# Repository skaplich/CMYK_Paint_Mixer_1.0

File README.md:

LOCKER : 91Y51          03-33-03

# CMYK_Paint_Mixer_1.0
ECE445 Project for FALL 2024

Color Sensor : https://www.adafruit.com/product/3779

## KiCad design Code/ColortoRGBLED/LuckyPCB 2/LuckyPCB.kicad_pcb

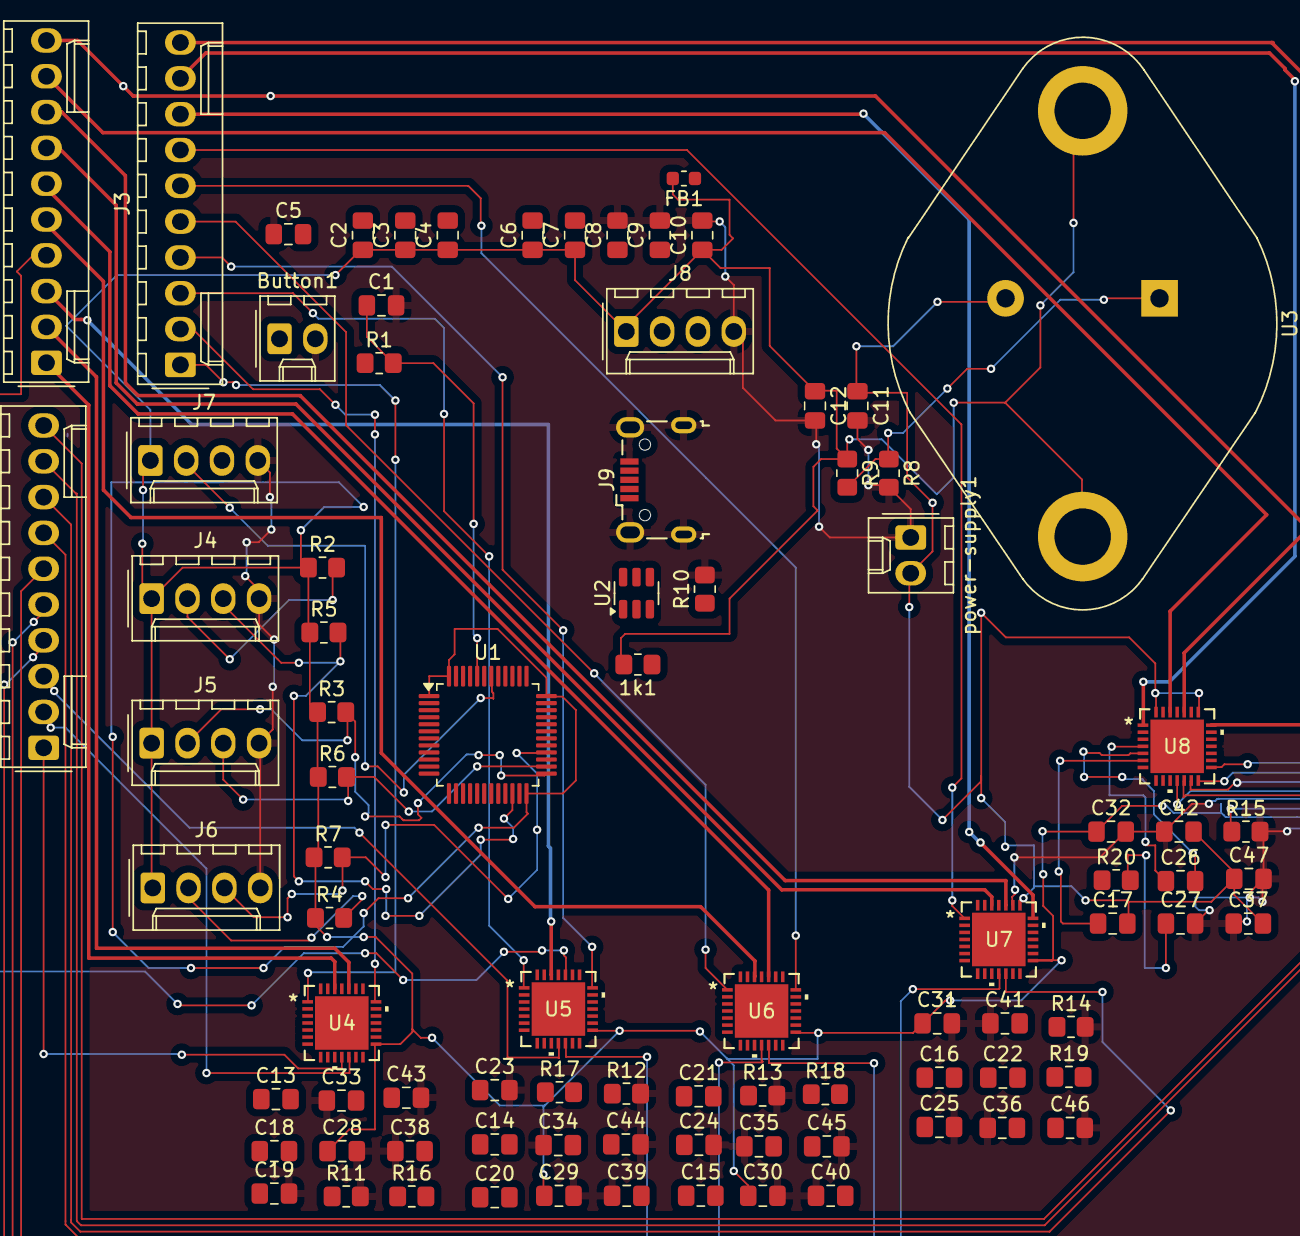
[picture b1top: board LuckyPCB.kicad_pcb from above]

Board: 2 copper layers, 88 parts (0 on the bottom side), 97 nets.

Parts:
1k1: R10; R_0805_2012Metric_Pad1.20x1.40mm_HandSolder
Button1: Conn_01x02; Molex_KK-254_AE-6410-02A_1x02_P2.54mm_Vertical
C1, C12: 1 uF; C_0805_2012Metric_Pad1.18x1.45mm_HandSolder
C2, C3, C4, C5, C6, C7, C33, C34, C35, C36, C37, C38, C39, C40, C41, C42: 100n; C_0805_2012Metric_Pad1.18x1.45mm_HandSolder
C8: 10n; C_0805_2012Metric_Pad1.18x1.45mm_HandSolder
C9, C10: 1u; C_0805_2012Metric_Pad1.18x1.45mm_HandSolder
C11: 0.1 uF; C_0805_2012Metric_Pad1.18x1.45mm_HandSolder
C13, C14, C15, C16, C17: 100 n/16v; C_0805_2012Metric_Pad1.18x1.45mm_HandSolder
C18, C20, C21, C22, C26: 22n/50v; C_0805_2012Metric_Pad1.18x1.45mm_HandSolder
C19, C23, C24, C25, C27: 2.2 uf; C_0805_2012Metric_Pad1.18x1.45mm_HandSolder
C28, C29, C30, C31, C32: 100n/50V; C_0805_2012Metric_Pad1.18x1.45mm_HandSolder
C43, C44, C45, C46, C47: 100 uF; C_0805_2012Metric_Pad1.18x1.45mm_HandSolder
FB1: FerriteBead; L_0603_1608Metric
J1, J2, J3: Conn_01x10_Pin; Molex_KK-254_AE-6410-10A_1x10_P2.54mm_Vertical
J4, J5, J6, J7, J8: Conn_01x04_Pin; Molex_KK-254_AE-6410-04A_1x04_P2.54mm_Vertical
J9: USB_B_Micro; USB_Micro-B_Wuerth_629105150521
R1: 10k; R_0805_2012Metric_Pad1.20x1.40mm_HandSolder
R2, R3, R4, R5, R6, R7: 1k5; R_0805_2012Metric_Pad1.20x1.40mm_HandSolder
R8: 390; R_0805_2012Metric_Pad1.20x1.40mm_HandSolder
R9: 240; R_0805_2012Metric_Pad1.20x1.40mm_HandSolder
R10: 100k; R_0805_2012Metric_Pad1.20x1.40mm_HandSolder
R11, R12, R13, R14, R15: 20k; R_0805_2012Metric_Pad1.20x1.40mm_HandSolder
R16, R17, R18, R19, R20: 18k; R_0805_2012Metric_Pad1.20x1.40mm_HandSolder
U1: STM32F103C8T6; LQFP-48_7x7mm_P0.5mm
U2: USBLC6-2SC6; SOT-23-6
U3: LM117_TO3; TO-3
U4, U5, U6, U7, U8: TMC2209-LA-T; QFN28_5X5_3X8_EPAD_TRI
power-supply1: Conn_01x02; Molex_KK-254_AE-6410-02A_1x02_P2.54mm_Vertical

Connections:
+3.3V: 1k1.2, C2.1, C3.1, C4.1, C6.1, C7.1, C10.1, C12.1, C28.1, C29.1, C30.1, C31.1, C32.1, FB1.2, J4.1, J5.1, J6.1, J7.1, J8.1, R2.1, R3.1, R4.1, R5.1, R6.1, R7.1, R9.1, U1.1 (VBAT), U1.24 (VDD), U1.36 (VDD), U1.48 (VDD), U3.3 (VO), U4.15 (VCC_IO), U5.15 (VCC_IO), U6.15 (VCC_IO), U7.15 (VCC_IO), U8.15 (VCC_IO)
+3.3VA: C8.1, C9.1, FB1.1, U1.9 (VDDA)
+24V: C11.1, C13.2, C14.2, C15.2, C16.2, C17.2, C33.2, C34.2, C35.2, C36.2, C37.2, C38.2, C39.2, C40.2, C41.2, C42.2, C43.1, C44.1, C45.1, C46.1, C47.1, U3.2 (VI), U4.22 (VS), U4.28 (VS), U5.22 (VS), U5.28 (VS), U6.22 (VS), U6.28 (VS), U7.22 (VS), U7.28 (VS), U8.22 (VS), U8.28 (VS), power-supply1.2
/I2C2_SCL: J4.2, R2.2, U1.21 (PB10)
/USART1_RX: J7.3, U1.43 (PB7)
DIAG-1: J2.1, U4.11 (DIAG)
DIAG-2: J2.3, U5.11 (DIAG)
DIAG-3: J2.5, U6.11 (DIAG)
DIAG-4: J2.7, U7.11 (DIAG)
DIAG-5: J2.9, U8.11 (DIAG)
DIR-1: U1.10 (PA0), U4.19 (DIR)
DIR-2: U1.12 (PA2), U5.19 (DIR)
DIR-3: U1.14 (PA4), U6.19 (DIR)
DIR-4: U1.16 (PA6), U7.19 (DIR)
DIR-5: U1.29 (PA8), U8.19 (DIR)
GND: Button1.2, C1.2, C5.1, C8.2, C9.2, C10.2, C11.2, C12.2, C19.2, C23.2, C24.2, C25.2, C27.2, C28.2, C29.2, C30.2, C31.2, C32.2, C33.1, C34.1, C35.1, C36.1, C37.1, C38.1, C39.1, C40.1, C41.1, C42.1, C43.2, C44.2, C45.2, C46.2, C47.2, J4.4, J5.4, J6.4, J7.4, J8.4, J9.5 (GND), J9.6 (Shield), R8.2, R10.2, R11.2, R12.2, R13.2, R14.2, R15.2, U1.8 (VSSA), U1.23 (VSS), U1.35 (VSS), U1.47 (VSS), U2.2 (GND), U4.2 (ENN), U4.3 (GND), U4.13 (CLK), U4.18 (GND), U4.23 (BRA), U4.27 (BRB), U4.29 (EPAD), U5.2 (ENN), U5.3 (GND), U5.13 (CLK), U5.18 (GND), U5.23 (BRA), U5.27 (BRB), U5.29 (EPAD), U6.2 (ENN), U6.3 (GND), U6.13 (CLK), U6.18 (GND), U6.23 (BRA), U6.27 (BRB), U6.29 (EPAD), U7.2 (ENN), U7.3 (GND), U7.13 (CLK), U7.18 (GND), U7.23 (BRA), U7.27 (BRB), U7.29 (EPAD), U8.2 (ENN), U8.3 (GND), U8.13 (CLK), U8.18 (GND), U8.23 (BRA), U8.27 (BRB), U8.29 (EPAD), power-supply1.1
INDEX-1: J2.2, U4.12 (INDEX)
INDEX-2: J2.4, U5.12 (INDEX)
INDEX-3: J2.6, U6.12 (INDEX)
INDEX-4: J2.8, U7.12 (INDEX)
INDEX-5: J2.10, U8.12 (INDEX)
MS1: U1.18 (PB0), U4.9 (MS1_AD0), U5.9 (MS1_AD0), U6.9 (MS1_AD0), U7.9 (MS1_AD0), U8.9 (MS1_AD0)
MS2: U1.19 (PB1), U4.10 (MS2_AD1), U5.10 (MS2_AD1), U6.10 (MS2_AD1), U7.10 (MS2_AD1), U8.10 (MS2_AD1)
unnamed: Button1.1, R1.1
unnamed: C2.2, C3.2, C4.2, C6.2, C7.2
unnamed: J4.3, R5.2, U1.22 (PB11)
unnamed: J5.2, R3.2, U1.25 (PB12)
unnamed: J5.3, R6.2, U1.26 (PB13)
unnamed: J6.2, R4.2, U1.27 (PB14)
unnamed: J6.3, R7.2, U1.28 (PB15)
unnamed: J7.2, U1.42 (PB6)
unnamed: J8.2, U1.34 (PA13)
unnamed: J8.3, U1.37 (PA14)
unnamed: J9.3 (D+), U2.6 (I/O1)
unnamed: J9.2 (D-), U2.1 (I/O1)
unnamed: J9.4 (ID), R10.1
unnamed: J9.1 (VBUS), U2.5 (VBUS)
unnamed: C1.1, R1.2, U1.44 (BOOT0)
unnamed: C5.2, U1.7 (NRST)
unnamed: U1.32 (PA11), U2.3 (I/O2)
unnamed: 1k1.1, U1.33 (PA12), U2.4 (I/O2)
unnamed: R8.1, R9.2, U3.1 (ADJ)
unnamed: C19.1, R16.2, U4.8 (5VOUT)
unnamed: C18.2, U4.5 (CPI)
unnamed: C18.1, U4.4 (CPO)
unnamed: R11.1, U4.14 (PDN_UART)
unnamed: C13.1, U4.6 (VCP)
unnamed: R16.1, U4.17 (VREF)
unnamed: C23.1, R17.2, U5.8 (5VOUT)
unnamed: C20.2, U5.5 (CPI)
unnamed: C20.1, U5.4 (CPO)
unnamed: R12.1, U5.14 (PDN_UART)
unnamed: C14.1, U5.6 (VCP)
unnamed: R17.1, U5.17 (VREF)
unnamed: C24.1, R18.2, U6.8 (5VOUT)
unnamed: C21.2, U6.5 (CPI)
unnamed: C21.1, U6.4 (CPO)
unnamed: R13.1, U6.14 (PDN_UART)
unnamed: C15.1, U6.6 (VCP)
unnamed: R18.1, U6.17 (VREF)
unnamed: C25.1, R19.2, U7.8 (5VOUT)
unnamed: C22.2, U7.5 (CPI)
unnamed: C22.1, U7.4 (CPO)
unnamed: R14.1, U7.14 (PDN_UART)
unnamed: C16.1, U7.6 (VCP)
unnamed: R19.1, U7.17 (VREF)
unnamed: C27.1, R20.2, U8.8 (5VOUT)
unnamed: C26.2, U8.5 (CPI)
unnamed: C26.1, U8.4 (CPO)
unnamed: R15.1, U8.14 (PDN_UART)
unnamed: C17.1, U8.6 (VCP)
unnamed: R20.1, U8.17 (VREF)
OA1-1: J1.2, U4.24 (OA1)
OA1-2: J1.4, U5.24 (OA1)
OA1-3: J1.6, U6.24 (OA1)
OA1-4: J1.8, U7.24 (OA1)
OA1-5: J1.10, U8.24 (OA1)
OA2-1: J3.2, U4.21 (OA2)
OA2-2: J3.4, U5.21 (OA2)
OA2-3: J3.6, U6.21 (OA2)
OA2-4: J3.8, U7.21 (OA2)
OA2-5: J3.10, U8.21 (OA2)
OB1-1: J1.1, U4.26 (OB1)
OB1-2: J1.3, U5.26 (OB1)
OB1-3: J1.5, U6.26 (OB1)
OB1-4: J1.7, U7.26 (OB1)
OB1-5: J1.9, U8.26 (OB1)
OB2-1: J3.1, U4.1 (OB2)
OB2-2: J3.3, U5.1 (OB2)
OB2-3: J3.5, U6.1 (OB2)
OB2-4: J3.7, U7.1 (OB2)
OB2-5: J3.9, U8.1 (OB2)
STEP-1: U1.11 (PA1), U4.16 (STEP)
STEP-2: U1.13 (PA3), U5.16 (STEP)
STEP-3: U1.15 (PA5), U6.16 (STEP)
STEP-4: U1.17 (PA7), U7.16 (STEP)
STEP-5: U1.30 (PA9), U8.16 (STEP)

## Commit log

2024-09-16 Create CADFiles
2024-09-16 Create notebooks
2024-10-20 Add files via upload
    Adding pcb project files
2024-11-12 Add files via upload
    These are the files I submitted for the second order of pcbway
    The gerber 2 folder has the gerber files I sent
2024-12-12 Adding Documentation
    documents and files saved over the course of the project
2024-12-12 adding code
    final code and additional libraries used and referenced
2024-12-12 Update Lab Notebook
2024-12-12 Create 10_11
2024-12-12 Create 10_18
2024-12-12 Create 10_25
2024-12-12 Create 11_1
2024-12-12 Create 11_8
2024-12-12 Create 11_15
2024-12-12 Create 11_22
2024-12-12 Update 10_11
2024-12-12 Update 10_18
2024-12-12 Update 10_25
2024-12-12 Update 11_1
2024-12-12 Update 11_8
2024-12-12 Update 11_15
2024-12-12 Update 11_22
2024-12-12 picture
    add
2024-12-12 Update README.md
    first few weeks of docs
2024-12-12 pcbpic2
    pcbpic2
2024-12-13 Add Final Code
